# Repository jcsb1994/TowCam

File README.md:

# Underwater Automated TowCam
This project has been developped in collaboration with the EEL Laboratory, affiliated with California State University, Monterey Bay.
Its main purpose is to increase seafloor mapping efficiency by combining the speed of a boat to the cheaper price of a camera 
compared to an ROV.

This project uses custom 3D printed parts, custom fabricated parts, and stock products from manufacturer BlueRobotics (https://www.bluerobotics.com).

# Electronics Components

   <b>MICROCONTROLLERS (2)</b><br>
    1. Arduino in the boat to be used as a controller, connected via serial to the other Arduino.
    2. Arduino in the submarine's enclosure.
      Serial communication between 2 arduinos: SoftwareSerial and AltSoftSerial libraries were used to clear RX and TX pins for debugging

   <b>SENSORS (3)</b><br>
    1. linear potentiometer<br>
      INPUT PIN: Analog, pullup<br>
    2. Pressure sensor<br>
      INPUT PIN: requires MS5837 Arduino Library.
      3V3 LOGIC: needs a I2C Level Converter between arduino and sensor to operate http://docs.bluerobotics.com/level-converter/#introduction<br>
    3. altimeter<br>
      INPUT PIN: 5 (RX of its own softwareSerial instance)
      Aiming directly under the tow camera.
      Vertical positioning: For now, no second SONAR: will be using the GoPro to locate incoming obstacles

   <b>ACTUATORS (3)</b>
    1. linear actuator (taken from the Newton gripper)<br>
      output PIN: digital, requires Servo library
      3V3 LOGIC: needs a I2C Level Converter between arduino and actuator to operate http://docs.bluerobotics.com/level-converter/#introduction<br>
    2. Servo motor (controlling the GoPro mount angle)<br>
      output PIN: digital, requires Servo library<br>
    3. Lumen light by blue robotics<br>
      output PIN: digital, requires Servo library

# Mechanical Components

<b>BlueRobotics products</b><br>
https://www.bluerobotics.com/store/watertight-enclosures/3-series/wte3-asm-r1/#configuration
https://www.bluerobotics.com/store/sensors-sonars-cameras/sensors/bar30-sensor-r1/
https://www.bluerobotics.com/store/thrusters/grippers/newton-gripper-asm-r1-rp/
https://www.bluerobotics.com/store/thrusters/lights/lumen-r2-rp/   <br>
SONAR Altimeter: <b> not in stocks (yet) </b>

<b>3D printed parts</b><br>
*All 3D printed parts are available in the stl_files folder

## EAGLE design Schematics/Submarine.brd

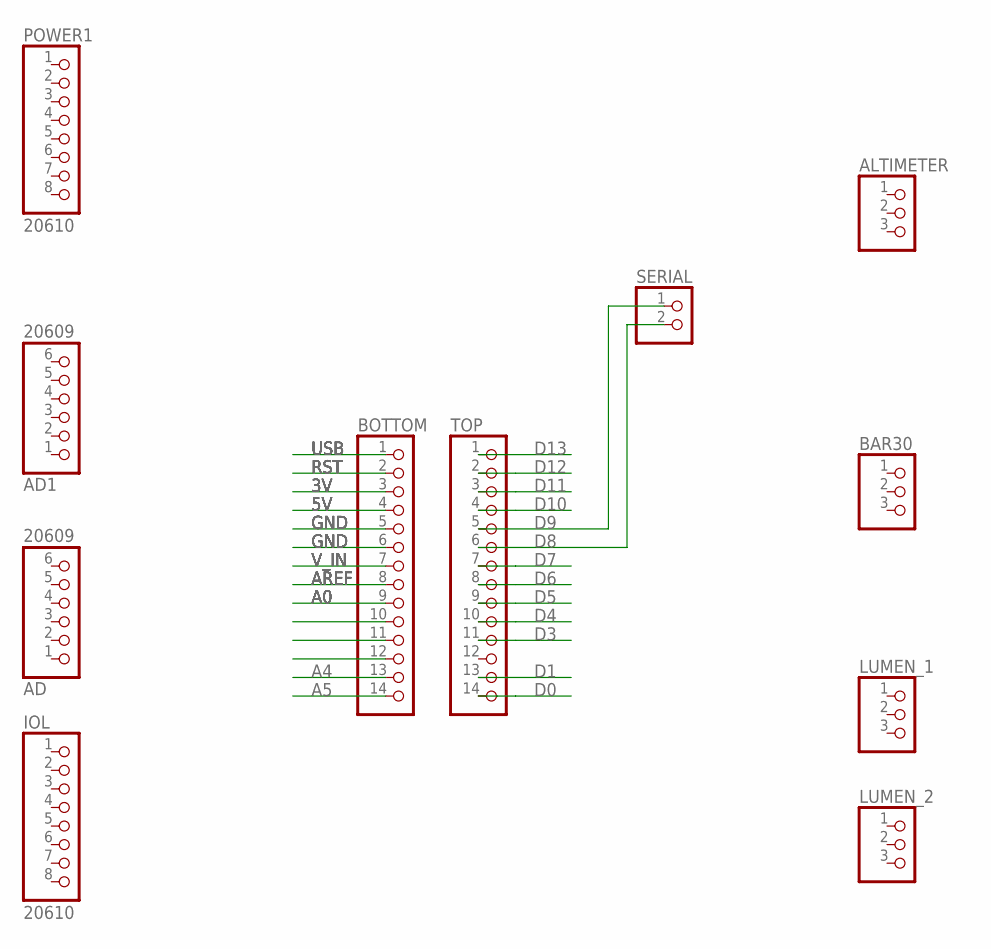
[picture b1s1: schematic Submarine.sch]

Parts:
AD, AD1: 20609; 1X06_ROUND
ALTIMETER: PINHD-1X3; 1X03
BAR30: PINHD-1X3; 1X03
BOTTOM: PINHD-1X14; 1X14
IOL: 20610; 1X08_ROUND
LUMEN_1, LUMEN_2: PINHD-1X3; 1X03
POWER1: 20610; 1X08_ROUND_70
SERIAL: PINHD-1X2; 1X02
TOP: PINHD-1X14; 1X14

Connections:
3V: BOTTOM.3
5V: BOTTOM.4
A0: BOTTOM.9
A4: BOTTOM.13
A5: BOTTOM.14
AREF: BOTTOM.8
D0: TOP.14
D1: TOP.13
D3: TOP.11
D4: TOP.10
D5: TOP.9
D6: TOP.8
D7: TOP.7
D8: SERIAL.2, TOP.6
D9: SERIAL.1, TOP.5
D10: TOP.4
D11: TOP.3
D12: TOP.2
D13: TOP.1
GND: BOTTOM.5, BOTTOM.6
RST: BOTTOM.2
USB: BOTTOM.1
V_IN: BOTTOM.7

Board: 2 copper layers, 11 parts (0 on the bottom side), 3 nets, no tracks yet.

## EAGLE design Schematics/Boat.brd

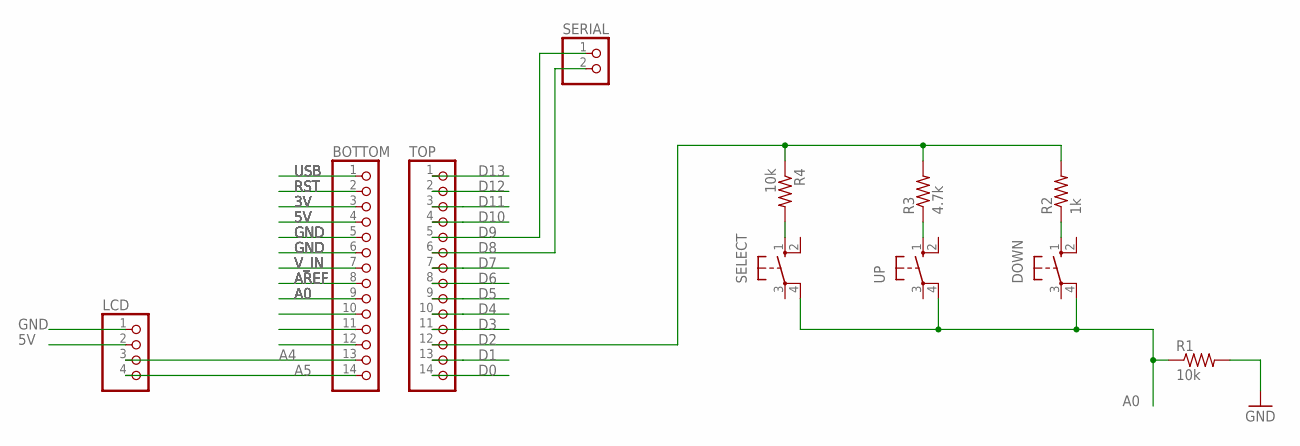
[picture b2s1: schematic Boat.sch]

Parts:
BOTTOM: PINHD-1X14; 1X14
DOWN: 10-XX; B3F-10XX
LCD: PINHD-1X4; 1X04
R1, R4: 10k; 0204/7
R2: 1k; 0204/7
R3: 4.7k; 0204/7
SELECT: 10-XX; B3F-10XX
SERIAL: PINHD-1X2; 1X02
TOP: PINHD-1X14; 1X14
UP: 10-XX; B3F-10XX

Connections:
3V: BOTTOM.3
5V: BOTTOM.4, LCD.2
A0: BOTTOM.9, DOWN.4 (P1), R1.1, SELECT.4 (P1), UP.4 (P1)
A4: BOTTOM.13, LCD.3
A5: BOTTOM.14, LCD.4
AREF: BOTTOM.8
D0: TOP.14
D1: TOP.13
D2: R2.2, R3.2, R4.1, TOP.12
D3: TOP.11
D4: TOP.10
D5: TOP.9
D6: TOP.8
D7: TOP.7
D8: SERIAL.2, TOP.6
D9: SERIAL.1, TOP.5
D10: TOP.4
D11: TOP.3
D12: TOP.2
D13: TOP.1
GND: BOTTOM.5, BOTTOM.6, LCD.1, R1.2
unnamed: R4.2, SELECT.1 (S)
unnamed: R3.1, UP.1 (S)
unnamed: DOWN.1 (S), R2.1
RST: BOTTOM.2
USB: BOTTOM.1
V_IN: BOTTOM.7

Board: 2 copper layers, 11 parts (0 on the bottom side), 11 nets, no tracks yet.

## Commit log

2018-12-15 Adding Arduino Code
    These versions are almost final. The boat controller is, but the submarine code needs correction on the PID and serial delays.
2018-12-16 Add serial version of menu for debugging when no LCD screen
2018-12-16 Update README.md
    Added a few components in the list, and cleaned titles
2018-12-16 forgot a </b> on README
2019-01-28 01/28/2018: added stl files and schematics
    The whole_project_simplified_schematic needs to be checked to make sure there are no mistakes. Is the way grounds are connected between the boat battery and submarine ok? etc.
2019-02-19 added simulated image

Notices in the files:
parts and their libraries:
microbuilder: This work is placed in the public domain, and may be freely used for commercial and non-commercial work with the following conditions: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
